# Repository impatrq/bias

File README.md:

# BIAS: Brain-Intelligence Artificial System
<div style="text-align: center;">

</div>

[Video de Presentación](https://youtu.be/uJyJxOkbonA?si=HoqrQriFnUhKq0Xh)

## Descripción del Proyecto

BIAS es un proyecto innovador que busca mejorar la movilidad de las personas con discapacidades motrices a través de una **silla de ruedas controlada por señales cerebrales**. Utilizamos tecnología de última generación para crear un sistema que interprete las señales eléctricas del cerebro y las traduzca en movimientos precisos para la silla.

## Características principales

- **Control mental**: Movimiento de la silla mediante señales cerebrales captadas por electrodos.
- **Procesador**: Uso de una Raspberry Pi 4 para el procesamiento de las señales.
- **Motor eficiente**: Sistema de motores controlados para movimientos suaves y seguros.
- **Interfaz adaptable**: Personalización según las necesidades del usuario.

## Tecnologías utilizadas

- **Electrodos** para captar las señales cerebrales.
- **Raspberry Pi 4** para el procesamiento de datos.
- **Python y C** para el desarrollo del software y control de la IA.
- **Diseño PCB personalizado** para la integración de los componentes.
- **Motores DC** controlados por puentes H.

## Estructura del Equipo

| Integrante          | Responsabilidad                               |
|---------------------|-----------------------------------------------|
| **Nicolás Adell**        | Programación de la IA y procesamiento de señales                       |
| **Luca De Blasi**        | Código para los motores                       |
| **Ian Gil Soria**        | Diseño de las placas PCB                      |
| **Danilo Díaz**        | Desarrollo de puentes H y drivers de motor    |
| **Luciano Montenegro**        | Documentación y asistencia técnica            |
| **Santiago Sojka**   | Marketing, diseño web y estructura de la silla|

## Contacto

- **LinkTree**: [Aquí](https://linktr.ee/biasproject?fbclid=PAZXh0bgNhZW0CMTEAAabechGqsvT3-QW-yQmUXelS48TQTC5eHy8vA9WU8YvmVHwiVOr6TlDTsC8_aem__CdOJhCiWx7UtaIUtjac-A)
- **Correo**: [bias.project@gmail.com](mailto:https://www.instagram.com/proyecto.bias/)
- **Instagram**: [@proyecto.bias](https://www.instagram.com/proyecto.bias)
- **Pagina Web**: [Aquí](https://sojkaa.github.io/BIAS-WEB/)

*BIAS 2024 - Todos los derechos reservados*

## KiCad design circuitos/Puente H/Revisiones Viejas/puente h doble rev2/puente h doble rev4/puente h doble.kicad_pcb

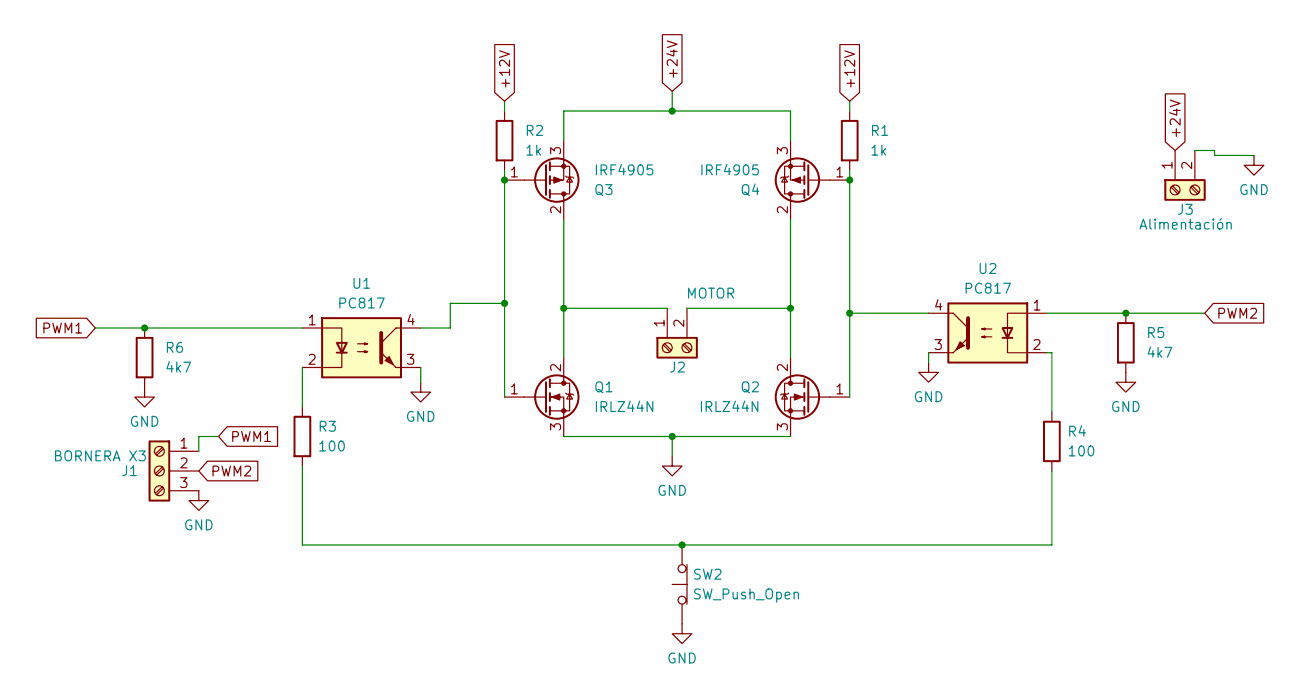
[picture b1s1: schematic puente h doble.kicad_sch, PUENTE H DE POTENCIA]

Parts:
J1: BORNERA X3; PinHeader_1x03_P2.54mm_Vertical
J2: MOTOR; TerminalBlock_Dinkle_DT-55-B01X-02_P10.00mm
J3: Alimentación; TerminalBlock_Dinkle_DT-55-B01X-02_P10.00mm
Q1, Q2: IRLZ44N; to-220 editado
Q3, Q4: IRF4905; to-220 editado
R1, R2: 1k; R_Axial_DIN0614_L14.3mm_D5.7mm_P20.32mm_Horizontal
R3, R4: 100; R_Axial_DIN0614_L14.3mm_D5.7mm_P20.32mm_Horizontal
R5, R6: 4k7; R_Axial_DIN0614_L14.3mm_D5.7mm_P20.32mm_Horizontal
SW2: SW_Push_Open; SW_CW_GPTS203211B
U1, U2: PC817; DIP-4_W7.62mm

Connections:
+12V: R1.1, R2.1
+24V: J3.1, Q3.3 (S), Q4.3 (S)
GND: J1.3, J3.2, Q1.3 (S), Q2.3 (S), R5.2, R6.2, SW2.1 (A), U1.3, U2.3
unnamed: J2.1, Q1.2 (D), Q3.2 (D)
unnamed: J2.2, Q2.2 (D), Q4.2 (D)
unnamed: Q1.1 (G), Q3.1 (G), R2.2, U1.4
unnamed: Q2.1 (G), Q4.1 (G), R1.2, U2.4
unnamed: R3.1, U1.2
unnamed: R4.1, U2.2
unnamed: R3.2, R4.2, SW2.2 (B)
PWM1: J1.1, R6.1, U1.1
PWM2: J1.2, R5.1, U2.1

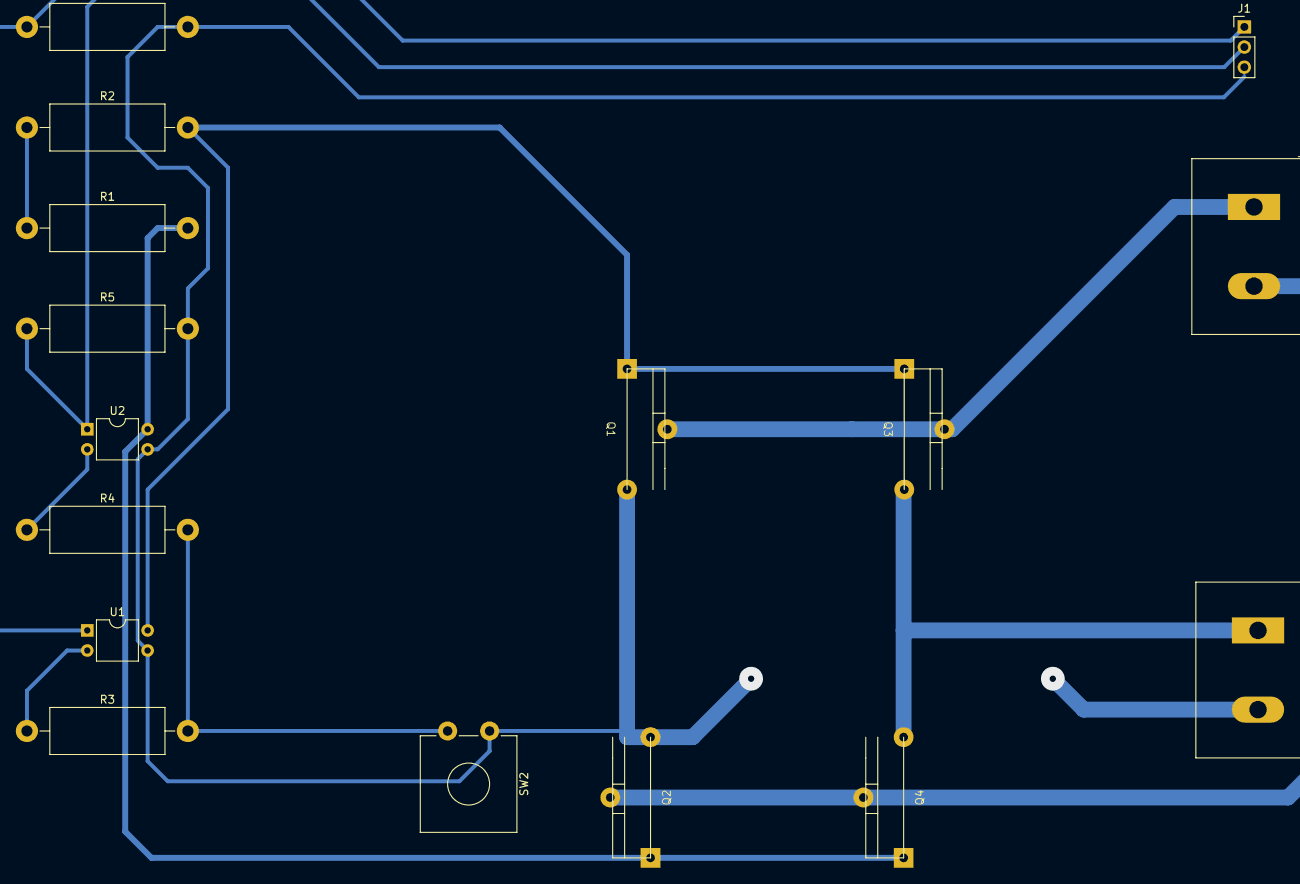
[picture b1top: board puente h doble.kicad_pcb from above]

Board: 2 copper layers, 16 parts (0 on the bottom side), 12 nets.

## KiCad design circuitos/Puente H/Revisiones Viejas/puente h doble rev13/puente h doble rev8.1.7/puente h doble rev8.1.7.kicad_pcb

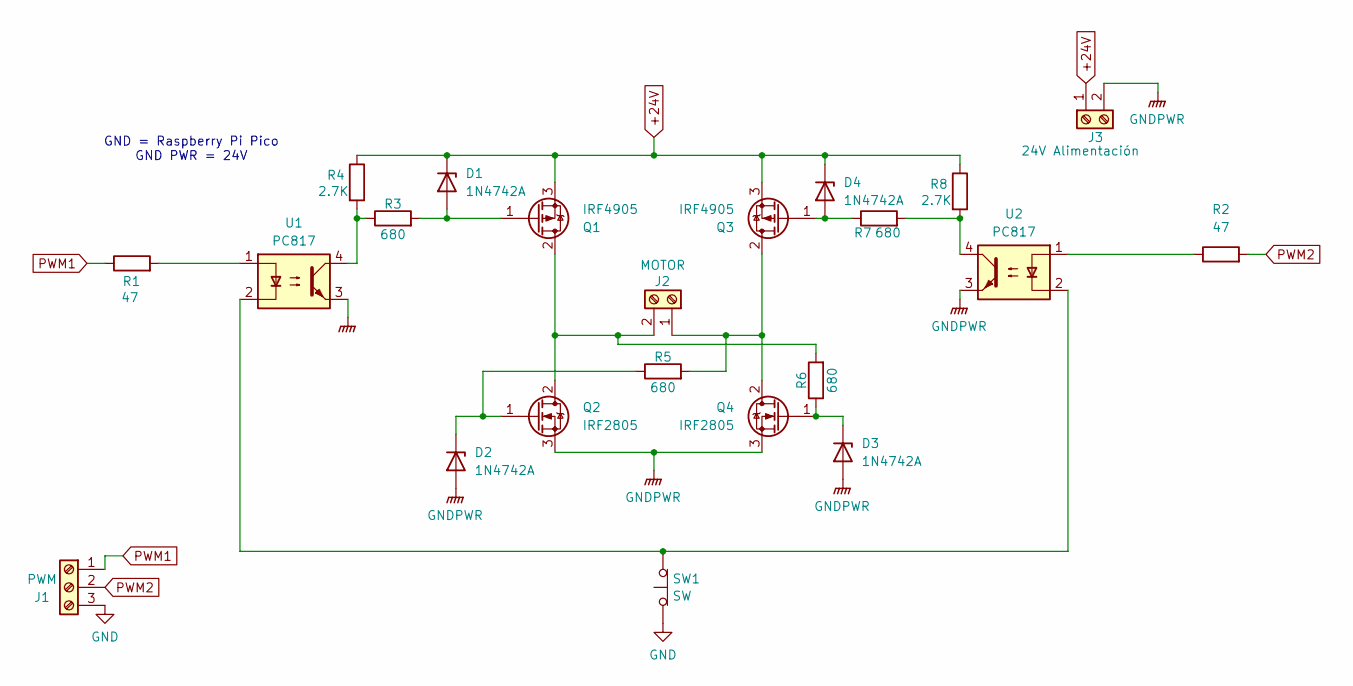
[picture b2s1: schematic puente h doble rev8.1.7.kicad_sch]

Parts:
D1, D2, D3, D4: 1N4742A; D_DO-41_SOD81_P10.16mm_Horizontal
J1: PWM; PinHeader_1x03_P2.54mm_Vertical
J2: MOTOR; TerminalBlock_Dinkle_DT-55-B01X-02_P10.00mm
J3: 24V Alimentación; TerminalBlock_Dinkle_DT-55-B01X-02_P10.00mm
Q1, Q3: IRF4905; TO-220-3_Vertical
Q2, Q4: IRF2805; TO-220-3_Vertical
R1, R2: 47; R_Axial_DIN0309_L9.0mm_D3.2mm_P12.70mm_Horizontal
R3, R5, R6, R7: 680; R_Axial_DIN0309_L9.0mm_D3.2mm_P12.70mm_Horizontal
R4, R8: 2.7K; R_Axial_DIN0309_L9.0mm_D3.2mm_P12.70mm_Horizontal
SW1: SW; PinHeader_1x02_P2.54mm_Vertical
U1, U2: PC817; DIP-4_W7.62mm

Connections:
+24V: D1.1 (K), D4.1 (K), J3.1, Q1.3 (S), Q3.3 (S), R4.1, R8.1
GNDPWR: D2.2 (A), D3.2 (A), J3.2, Q2.3 (S), Q4.3 (S), U1.3, U2.3
unnamed: D1.2 (A), Q1.1 (G), R3.2
unnamed: D2.1 (K), Q2.1 (G), R5.1
unnamed: D3.1 (K), Q4.1 (G), R6.1
unnamed: D4.2 (A), Q3.1 (G), R7.1
unnamed: J1.3, SW1.1 (A)
unnamed: J2.1, Q3.2 (D), Q4.2 (D), R5.2
unnamed: J2.2, Q1.2 (D), Q2.2 (D), R6.2
unnamed: R1.2, U1.1
unnamed: R2.1, U2.1
unnamed: R3.1, R4.2, U1.4
unnamed: R7.2, R8.2, U2.4
unnamed 14: SW1.2 (B), U1.2, U2.2; also elsewhere on the board
PWM1: J1.1, R1.1; also elsewhere on the board
PWM2: J1.2, R2.2; also elsewhere on the board

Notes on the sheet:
GND = Raspberry Pi Pico GND PWR = 24V

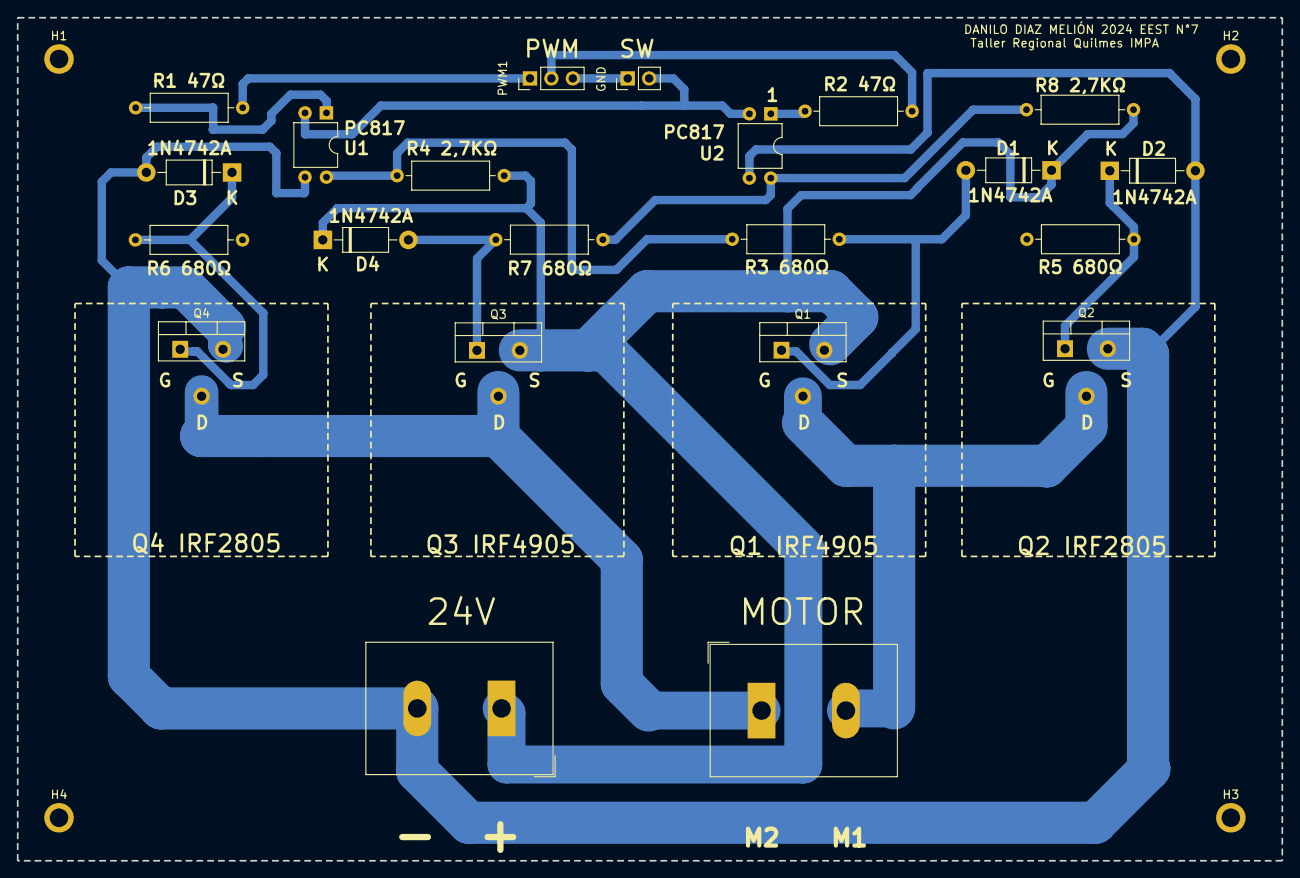
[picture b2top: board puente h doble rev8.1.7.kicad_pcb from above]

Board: 2 copper layers, 150.0 x 100.0 mm, 26 parts (0 on the bottom side), 16 nets.

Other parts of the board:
GND: SW; PinHeader_1x02_P2.54mm_Vertical
H1, H2, H3, H4: MountingHole_2.2mm_M2_ISO7380_Pad
PWM1: PWM; PinHeader_1x03_P2.54mm_Vertical

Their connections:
GND: GND.1 (A), PWM1.3
unnamed 14: GND.2 (B); also elsewhere on the board
PWM1: PWM1.1; also elsewhere on the board
PWM2: PWM1.2; also elsewhere on the board

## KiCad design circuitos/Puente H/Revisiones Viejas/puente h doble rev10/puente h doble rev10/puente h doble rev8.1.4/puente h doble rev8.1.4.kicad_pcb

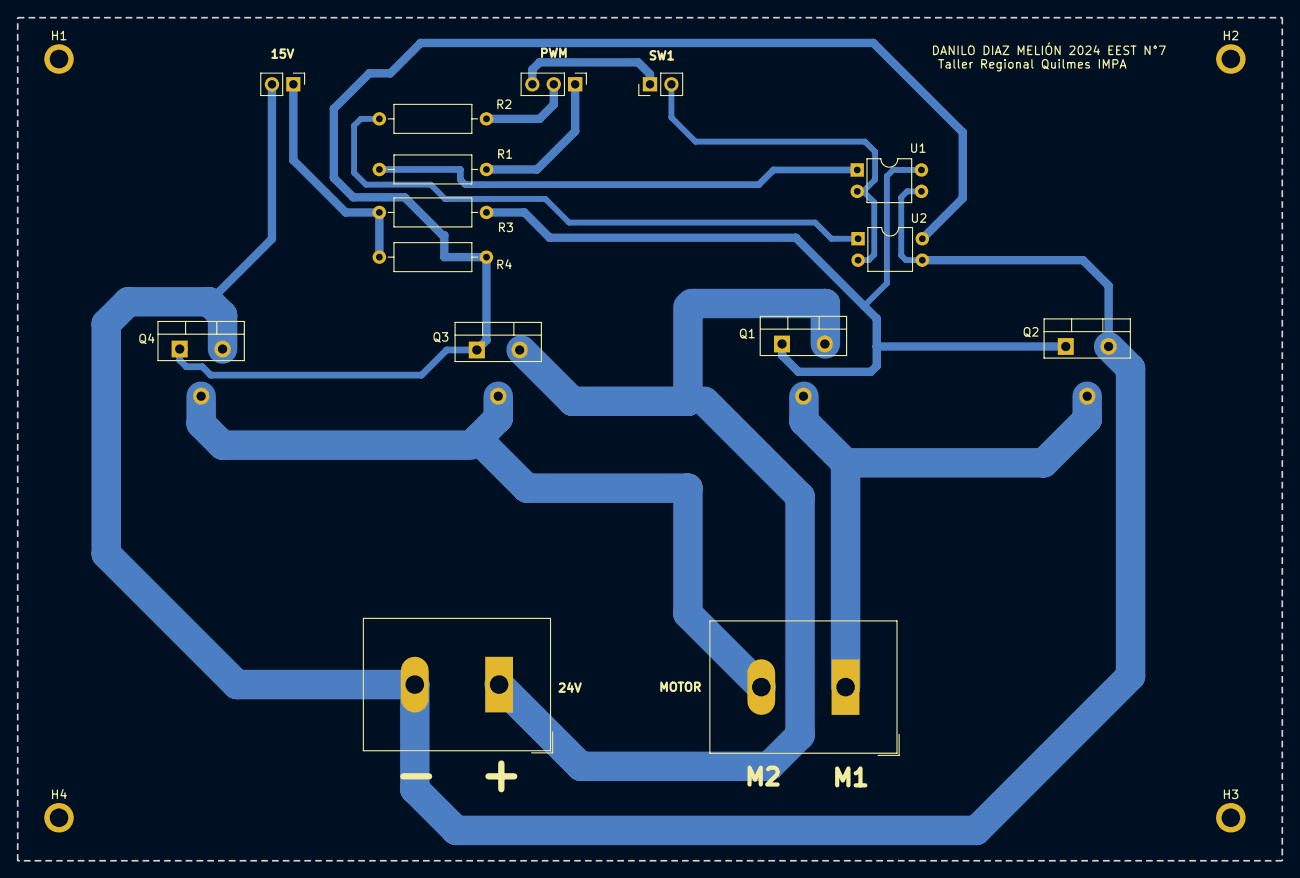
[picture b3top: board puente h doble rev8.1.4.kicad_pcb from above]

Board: 2 copper layers, 150.0 x 100.0 mm, 19 parts (0 on the bottom side), 13 nets.

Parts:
15V: 15V Alimentación; PinHeader_1x02_P2.54mm_Vertical
24V: 24V Alimentación; TerminalBlock_Dinkle_DT-55-B01X-02_P10.00mm
H1, H2, H3, H4: MountingHole_2.2mm_M2_ISO7380_Pad
MOTOR: MOTOR; TerminalBlock_Dinkle_DT-55-B01X-02_P10.00mm
PWM: PWM; PinHeader_1x03_P2.54mm_Vertical
Q1, Q3: IRF4905; TO-220-3_Vertical
Q2, Q4: IRLZ44N; TO-220-3_Vertical
R1, R2: 180; R_Axial_DIN0309_L9.0mm_D3.2mm_P12.70mm_Horizontal
R3, R4: 1k; R_Axial_DIN0309_L9.0mm_D3.2mm_P12.70mm_Horizontal
SW1: SW; PinHeader_1x02_P2.54mm_Vertical
U1, U2: PC817; DIP-4_W7.62mm

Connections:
+15V: 15V.1, R3.1, R4.1
+24V: 24V.1, Q1.3 (S), Q3.3 (S)
GND: PWM.3, SW1.1 (A)
GNDPWR: 15V.2, 24V.2, Q2.3 (S), Q4.3 (S), U1.3, U2.3
unnamed: MOTOR.1, Q1.2 (D), Q2.2 (D)
unnamed: MOTOR.2, Q3.2 (D), Q4.2 (D)
unnamed: Q1.1 (G), Q2.1 (G), R3.2, U1.4
unnamed: Q3.1 (G), Q4.1 (G), R4.2, U2.4
unnamed: R1.2, U1.1
unnamed: R2.1, U2.1
unnamed: SW1.2 (B), U1.2, U2.2
PWM1: PWM.1, R1.1
PWM2: PWM.2, R2.2

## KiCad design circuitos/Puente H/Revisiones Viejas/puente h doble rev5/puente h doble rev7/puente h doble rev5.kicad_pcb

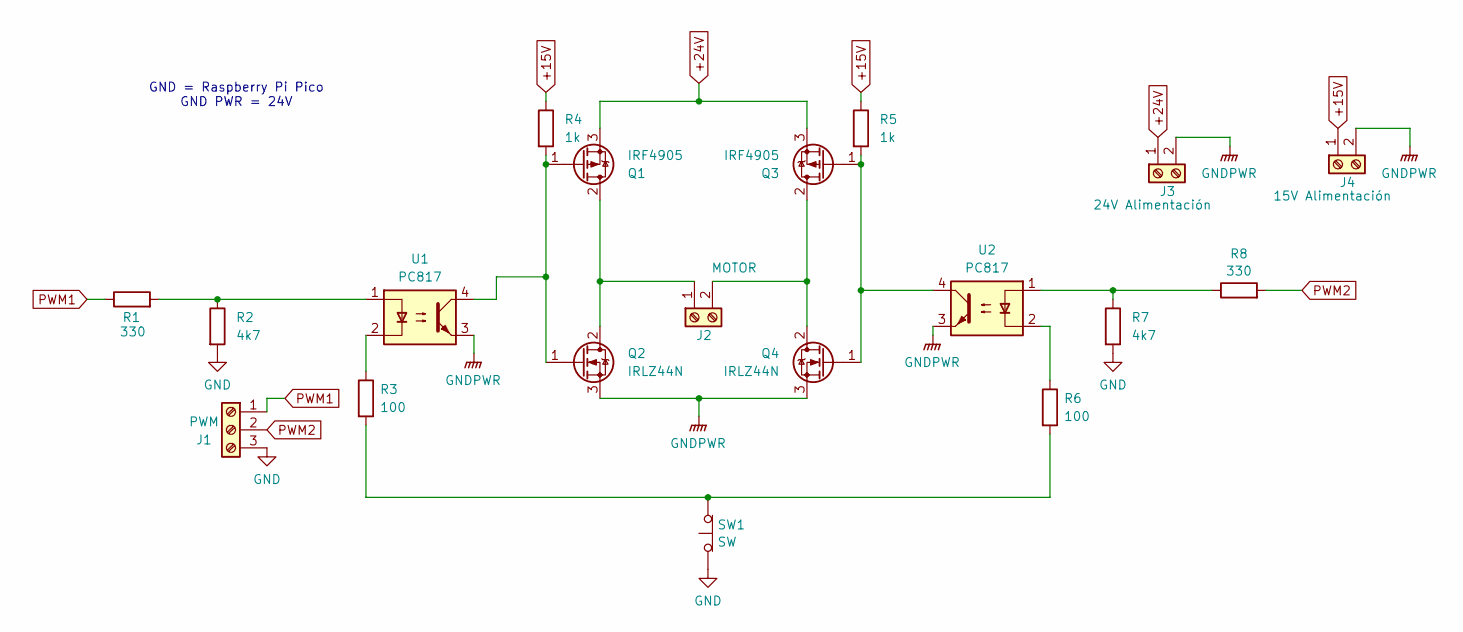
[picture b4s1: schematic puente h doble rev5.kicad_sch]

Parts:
J1: PWM; PinHeader_1x03_P2.54mm_Vertical
J2: MOTOR; TerminalBlock_Dinkle_DT-55-B01X-02_P10.00mm
J3: 24V Alimentación; TerminalBlock_Dinkle_DT-55-B01X-02_P10.00mm
J4: 15V Alimentación; PinHeader_1x02_P2.54mm_Vertical
Q1, Q3: IRF4905; TO-220-3_Vertical
Q2, Q4: IRLZ44N; TO-220-3_Vertical
R1, R8: 330; R_Axial_DIN0309_L9.0mm_D3.2mm_P12.70mm_Horizontal
R2, R7: 4k7; R_Axial_DIN0309_L9.0mm_D3.2mm_P12.70mm_Horizontal
R3, R6: 100; R_Axial_DIN0309_L9.0mm_D3.2mm_P12.70mm_Horizontal
R4, R5: 1k; R_Axial_DIN0309_L9.0mm_D3.2mm_P12.70mm_Horizontal
SW1: SW; PinHeader_1x02_P2.54mm_Vertical
U1, U2: PC817; DIP-4_W7.62mm

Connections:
+15V: J4.1, R4.1, R5.1
+24V: J3.1, Q1.3 (S), Q3.3 (S)
GND: J1.3, R2.2, R7.2, SW1.1 (A)
GNDPWR: J3.2, J4.2, Q2.3 (S), Q4.3 (S), U1.3, U2.3
unnamed: J2.1, Q1.2 (D), Q2.2 (D)
unnamed: J2.2, Q3.2 (D), Q4.2 (D)
unnamed: Q1.1 (G), Q2.1 (G), R4.2, U1.4
unnamed: Q3.1 (G), Q4.1 (G), R5.2, U2.4
unnamed: R1.2, R2.1, U1.1
unnamed: R3.1, U1.2
unnamed: R6.1, U2.2
unnamed: R7.1, R8.1, U2.1
unnamed: R3.2, R6.2, SW1.2 (B)
PWM1: J1.1, R1.1
PWM2: J1.2, R8.2

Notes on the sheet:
GND = Raspberry Pi Pico GND PWR = 24V

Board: 2 copper layers, 19 parts (0 on the bottom side), 15 nets, no tracks yet.

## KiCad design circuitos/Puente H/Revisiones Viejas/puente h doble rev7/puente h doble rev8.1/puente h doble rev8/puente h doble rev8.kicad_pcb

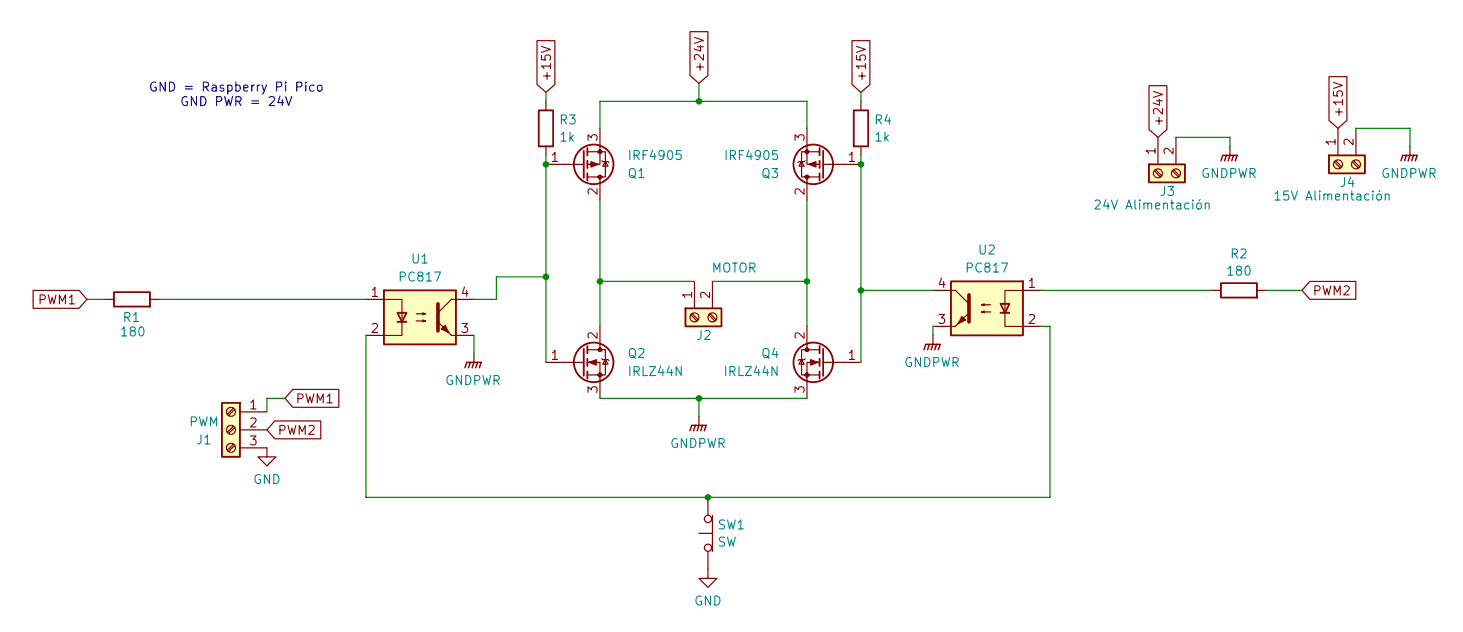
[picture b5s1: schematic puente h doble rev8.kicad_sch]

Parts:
J1: PWM; PinHeader_1x03_P2.54mm_Vertical
J2: MOTOR; TerminalBlock_Dinkle_DT-55-B01X-02_P10.00mm
J3: 24V Alimentación; TerminalBlock_Dinkle_DT-55-B01X-02_P10.00mm
J4: 15V Alimentación; PinHeader_1x02_P2.54mm_Vertical
Q1, Q3: IRF4905; TO-220-3_Vertical
Q2, Q4: IRLZ44N; TO-220-3_Vertical
R1, R2: 180; R_Axial_DIN0309_L9.0mm_D3.2mm_P12.70mm_Horizontal
R3, R4: 1k; R_Axial_DIN0309_L9.0mm_D3.2mm_P12.70mm_Horizontal
SW1: SW; PinHeader_1x02_P2.54mm_Vertical
U1, U2: PC817; DIP-4_W7.62mm

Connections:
+15V: J4.1, R3.1, R4.1
+24V: J3.1, Q1.3 (S), Q3.3 (S)
GND: J1.3, SW1.1 (A)
GNDPWR: J3.2, J4.2, Q2.3 (S), Q4.3 (S), U1.3, U2.3
unnamed: J2.1, Q1.2 (D), Q2.2 (D)
unnamed: J2.2, Q3.2 (D), Q4.2 (D)
unnamed: Q1.1 (G), Q2.1 (G), R3.2, U1.4
unnamed: Q3.1 (G), Q4.1 (G), R4.2, U2.4
unnamed: R1.2, U1.1
unnamed: R2.1, U2.1
unnamed: SW1.2 (B), U1.2, U2.2
PWM1: J1.1, R1.1
PWM2: J1.2, R2.2

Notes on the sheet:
GND = Raspberry Pi Pico GND PWR = 24V

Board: 2 copper layers, 15 parts (0 on the bottom side), 13 nets, no tracks yet.

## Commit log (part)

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2024-08-28 style: change variable name
2024-08-29 chore: files for extraction.c
2024-08-30 feat: add more ai features
2024-09-01 fix: change Bias class name for circular error
2024-09-01 feat: add possibility to try synthetic data
2024-09-01 fix: change format of synthetic data
2024-09-01 fix: adjust dimention of input layer
2024-09-01 refactor: generalize label map
2024-09-02 feat: add place to load dataset and to save to a path
2024-09-02 fix: change name variable
2024-09-02 chore: make statement well
2024-09-02 fix: modify bug
2024-09-03 chore: generalize variables
2024-09-03 fix: assert that list has certain requirements
2024-09-03 feat: add entropy as feature
2024-09-04 chore: comment layer
2024-09-04 feat: add PWM frequency
2024-09-04 feat: se añaden 3 codigos para el multithreading
    con el run_task.py se ejecutan los dos codigos
2024-09-05 feat: modificar app.py y borrar Emergencia
2024-09-05 feat: add README
2024-09-06 fix: change libraries imported names
2024-09-10 fix: change frequency
2024-09-10 feat: añado el movimiento de motores a la app
2024-09-11 feat: add datasets
2024-09-13 feat: cambio de referencia de variables
2024-09-14 feat: import dataset
2024-09-17 feat: add repository for npz dataset format
2024-09-17 chore: rename repository
2024-09-17 Feat: Agregar Imagenes del Sistema EEG
2024-09-18 chore: files to building
2024-09-19 feat: Subida de contenido de la carpeta técnica
    Aqui se adjuntaron todas las imágenes y códigos que están hasta el momento en la carpeta técnica
2024-09-20 fix: fix errors and delete folder with dataset referring to a repository
2024-09-20 Actualización del manual técnico
    Creación del indice "Desarrollo teórico" y sus subsecciones
2024-09-20 chore: delete redundant code
2024-09-21 Delete Página Web/component.jsx
    no sirve mas
2024-09-23 feat: add bci_dataset folder from another github
2024-09-23 fix: correccion de nombre de carpeta "docs" a "circuitos"
2024-09-23 fix: cambio de nombre a carpeta "PDFs EEG" a filtrosEEG
2024-09-23 Feat: Creacion de Carpetas "DLCs Kicad" y "SistemaOffset" ; Agregado del archivo de bornera KF301-3P en un comprimido
2024-09-23 Feat: Agregado el archivo del modelo del Operacional TL084 para Kicad en comprimido
2024-09-23 Feat: Agregado del archivo del modelo del Regulador LM7805 para Kicad en Comprimido
2024-09-23 Feat: Agregado del archivo del modelo del amplificador AD620AN para Kicad en Comprimido
2024-09-23 Feat: Agregado del archivo del modelo del Micro RP2040zero para Kicad en Comprimido
2024-09-23 feat: agregado del archivo del regulador lm7815 para Kicad en comprimido
2024-09-23 feat: agregado del archivo del Micro RPBRRY Pi4 para Kicad en comprimido
2024-09-23 feat: agregado del esquematico del Sistema de emergencia
2024-09-23 feat: agregado del modelo 3D del Sistema de Emergencias
2024-09-23 feat: agregado del modelo 3D del Sistema Offset
2024-09-23 feat: agregado del diseño PCB del sistema Offset
2024-09-23 feat: agregado del esquematico del Sistema de Alimentacion y Control
2024-09-23 feat: agregado del diseño PCB del sistema de alimentacion y control
2024-09-23 feat: agregado del modelo 3D del sistema de alimentacion y control
2024-09-23 feat: creacion carpeta Serigrafia
    se incluye el archivo del modeo del Logo del proyecto para Kicad en comprimido
2024-09-23 feat: se agrega simulacion de filtro pasa altos del sistema EEG
2024-09-25 feat: Actualización de carpeta técnica
    Añadido: Explicación de Jaula de Faraday y su aplicación
2024-09-25 feat: Explicación Puente H
    Se añadió la explicación teórica del Puente H, su aplicación e Imágenes.
2024-09-25 feat: añadir simulación (proteus) de puente h
2024-09-25 feat: añadir huella personalizada e imágenes a la página web
2024-09-26 chore: delete bci items without sense
2024-09-26 feat: Actualización de la carpeta técnica
2024-09-26 feat: Creacion de la carpeta "Filtrado"
2024-09-26 feat: Creación de la carpeta "Inteligencia Artificial" y "Motores"
2024-09-26 feat: Creación de la carpeta "Recepcion"
2024-09-26 feat: Organizacion de imagenes
2024-09-26 feat: Actualización del manual
2024-09-26 feat: añadir revisión 1 de puente h doble
2024-09-27 fix: not compiling code
2024-09-30 feat: añadir 2da simulación proteus 20/7
2024-09-30 feat: añadir versión número 3 de simulación (21/7)
2024-09-30 fix: change number of samples in the dataset
2024-09-30 fix: change incoherent dimentions
2024-09-30 fix: modify num of features
2024-09-30 fix: organizacion de carpeta
2024-09-30 Create Página Web
2024-09-30 feat: añado una tarea mas al multithreading
2024-09-30 feat: modifico el codigo run_task para que sea POO
2024-09-30 feat: Creación de carpeta Cableado
2024-09-30 feat: Actualización carpeta Cableado
2024-09-30 feat: Actualización de la carpeta "Cableado"
2024-09-30 feat: Creación de la carpeta "Excalidraw".
2024-09-30 feat: Actualización de carpeta "Cableado"
2024-09-30 feat: Organización de carpeta "Cableado"
2024-09-30 feat: Creación de la carpeta "Excalidraw"
2024-09-30 feat: añadir el multithreading a codigo app
2024-10-01 chore: building
2024-10-01 feat: añadir simulación proteus del puente h del 30/9
2024-10-01 feat: añadir las dos simulaciones de proteus del día 1/10
2024-10-03 feat: añado el sistema 10-20 al manual tecnico
2024-10-03 feat: añado el funcionamiento de los filtros
2024-10-03 feat: añado funcionamiento de Puente H al manual tecnico
2024-10-03 feat: reorganizar el manual tecnico
2024-10-04 feat: añado informacion importante al manual tecnico (otra vez)
2024-10-04 feat: Adjuntar Código del main.tex
2024-10-04 feat: Adjuntadas las imágenes utilizadas en el informe
2024-10-04 fix: eliminar el manual tecnico bugeado
2024-10-04 fix: modify iteration in the dataset
2024-10-04 feat: Creación de la explicación del Sistema de Emergencia
2024-10-04 feat: Actualización del informe técnico
2024-10-04 feat: Actualización Informe Descriptivo
2024-10-04 fix: prepare dataset to be trained
2024-10-04 feat: Creación del término "Referencias" de la carpeta técnica
2024-10-04 fix: change variables name
2024-10-04 feat: Creación del término "Cantidad de canales" y "Distintas Alimentaciones"
2024-10-05 feat: añadir trabajo en proteus 2/10
2024-10-05 feat: añadir trabajo proteus 4/10
2024-10-05 feat: añadir informe driver DS72K
2024-10-05 feat: añadir revisión vieja del puente H en KiCad
2024-10-05 feat: añadir revisión n°3 de kicad del puente h
2024-10-05 feat: añadir revisión n°5 del puente H kicad
2024-10-05 feat: añadir revisión n°6 del puente H kicad
2024-10-05 feat: añadir revisión n°7 del puente H kicad
2024-10-05 feat: añadir revisión n°8 del puente H kicad
2024-10-05 feat: añadir revisión n°10 del puente H kicad
2024-10-07 fix: combine all trials for 9 datasets
2024-10-08 feat: create umbrales.py
2024-10-09 feat: Subida de carpeta Excalidraw
2024-10-09 feat: añado info. al manual tecnico
    entre esta informacion se encuentra:
    una ampliaciona la jaula de faraday
    una ampliacion y modificacion al apartado EEG
    añadi un apartado de Raspberry Pi4
    añadi las columnas para luego poner fotos de los integrantes
2024-10-10 feat: añadir revisión 11 del Puente H
2024-10-10 feat: añadir revisión 12 puente h
2024-10-10 feat: añadir revisión 14 puente h
2024-10-10 feat: añadir huellas personalizadas del modelado 3D del puente H
2024-10-10 feat: añadir versión 10 de simulación del puente h en proteus
2024-10-10 fix: change segmentation function
2024-10-10 feat: Subida de codigos a la carpeta técnica
2024-10-10 feat: Subida de codigos
2024-10-10 feat: añado informacion relevante
2024-10-10 fix: modify dimention of layer
2024-10-10 chore: delete not used code
2024-10-10 feat: add SVC model
2024-10-10 feat: Actualizacion Carpeta de Campo
2024-10-11 feat: explicar los codigos
2024-10-11 feat: add metrics to the code
2024-10-12 feat: add csp
2024-10-12 fix: modify svm algorithm
2024-10-12 feat: add bwhaviour of svm
2024-10-12 feat: add signal segmentation
2024-10-12 feat: check dimentionality
2024-10-12 fix: reshaping
2024-10-12 fic: solve compiling error
2024-10-12 fix: change dimentionality of features
2024-10-12 chore: delete code commented
2024-10-12 chore: change variable names
2024-10-12 feat: add svm and cnn condition
2024-10-12 fix: change label binarizer
2024-10-13 fix: make system work
2024-10-13 feat: add model saving
2024-10-13 feat: add options to app
2024-10-13 chore: delete libraries not used
2024-10-13 fix: modify get_real_data function
2024-10-13 chore=change vaiiable name
2024-10-13 chore: building of files
2024-10-13 chore: delete spanish comments
2024-10-13 style: add comments
2024-10-13 fix: change mistakes
2024-10-13 fix: change statements
2024-10-13 fix: modify CSP
2024-10-13 fix: change signal dimention
2024-10-14 feat: add pipeline
2024-10-14 fix: corregir informacion sobre el proyecto erronea
2024-10-14 chore: delete file not used
2024-10-14 feat: Fotos de mayo
2024-10-14 feat: Fotos de junio
2024-10-14 feat: Fotos de abril
2024-10-14 feat: Fotos de marzo
2024-10-14 feat: Agregar personas a la carepta
2024-10-14 feat: Actualizacion PDF Carpeta tecnica
2024-10-14 feat: Imagenes de octubre
2024-10-14 fix: corregir informe de puente H con el modelo actualizado
2024-10-19 fix: modify compiling errors
2024-10-19 chore: building files
2024-10-22 README.md
2024-10-23 fix: add protection
2024-10-23 chore: files for building
2024-10-23 feat: add coleeg
2024-10-24 feat: Actualización de octubre
2024-10-24 feat: add EEGNet model
2024-10-24 feat: add coleeg code
2024-10-25 feat: eliminar codigos que no sirven y añadir multicore
2024-10-25 feat: añado archivo de "app" de multicore
2024-10-25 feat: .
2024-10-26 feat: add EEGNet with 63% of accracy
2024-10-26 feat: add saving model functionality
2024-10-28 feat: addapt dataset to differential voltages
2024-10-29 feat: añadir datasheet de IRF3205
2024-10-29 feat: añadir plano autocad de parte baja de gabinete del puente h
2024-10-29 feat: añadir plano autocad de costado corto de gabinete del puente h
2024-10-29 feat: añadir plano autocad de costado largo de gabinete del puente h
2024-10-29 feat: añadir plano autocad de varilla para disipadores del puente H
2024-10-29 fix: eliminar informe de Puente H desactualizado
2024-10-29 feat: añadir infografía
2024-10-31 fix: modify motors code
2024-10-31 fix: set frequency in reception to 250 Hz
2024-11-04 feat: Costado.stl
2024-11-04 feat: Parte frontal inferior
2024-11-04 feat: Parte frontal superior
2024-11-04 feat: Parte superior 1
2024-11-04 feat: Parte superior 2
2024-11-04 feat: Parte trasera
2024-11-05 feat: Corrección de ParteTrasera.stl
2024-11-06 feat: Corrección de dos modelos y STLs
2024-11-06 feat: STLs
2024-11-06 feat: Soporte STL
2024-11-07 Feat: actualizacion del PCB placa Offset
2024-11-07 Feat: Diseños Finales placa Offset
2024-11-07 Feat: Diseño Final Sistema Emergencias
2024-11-07 Feat: agrego simulacuiones placa de recepcion
2024-11-07 fix: change ReadMe
2024-11-07 Feat: Se agrega simulaciones y
    Placa de Recepcion y Alimentacion diseño final
2024-11-07 Feat: Esquematico final Recepcion y Alimentacion
2024-11-07 Feat: se agrega esquematico con vista detallada
2024-11-07 Feat: Se agrega diseño final placa Filtros EEG
2024-11-07 Feat: Se agrega diseño de interconexiones y carpeta
2024-11-08 feat: cambio el codigo de multiprocessing por uno secuencial
2024-11-08 feat: le añadi la parte de recepcion y graficar al codigo de core_run
2024-11-08 feat: le añado el codigo de la IA al codigo de core_run
2024-11-11 feat: añado el manual de usuario
2024-11-11 feat: añado los puntos en donde colocar los electrodos al manual de usuario
2024-11-11 feat: vuelvo a subir el pdf del manual de usuario
2024-11-15 feat: añado la tarea de los filtros al multicore
2024-11-26 feat: add shallow convnet
2024-11-26 build: files added when compiling
2024-11-26 feat: add simulations
2024-11-26 docs: add presentation video
2024-11-26 feat: Elementos de alcance inconclusos
2024-11-26 feat: add Linktree to ReadMe
2024-11-27 feat: añadir Banner BIAS
2024-11-27 fix: reorganizar carpeta Modelado 3D
2024-11-27 docs: add web page to ReadMe
2024-11-27 fix: update README.md
2024-11-27 feat: FACTURA BIAS
2024-11-28 docs: add presentation
2024-11-29 fix: actualizar presentación
